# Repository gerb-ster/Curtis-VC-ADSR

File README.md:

# Curtis VC ADSR

A voltage controlled ADSR enveloppe generator based on the CEM 3310

## Status: Finished

- done: first schematic & board design
- done: breadboard and test
- done: design frontpanel
- done: order PCB and build prototype

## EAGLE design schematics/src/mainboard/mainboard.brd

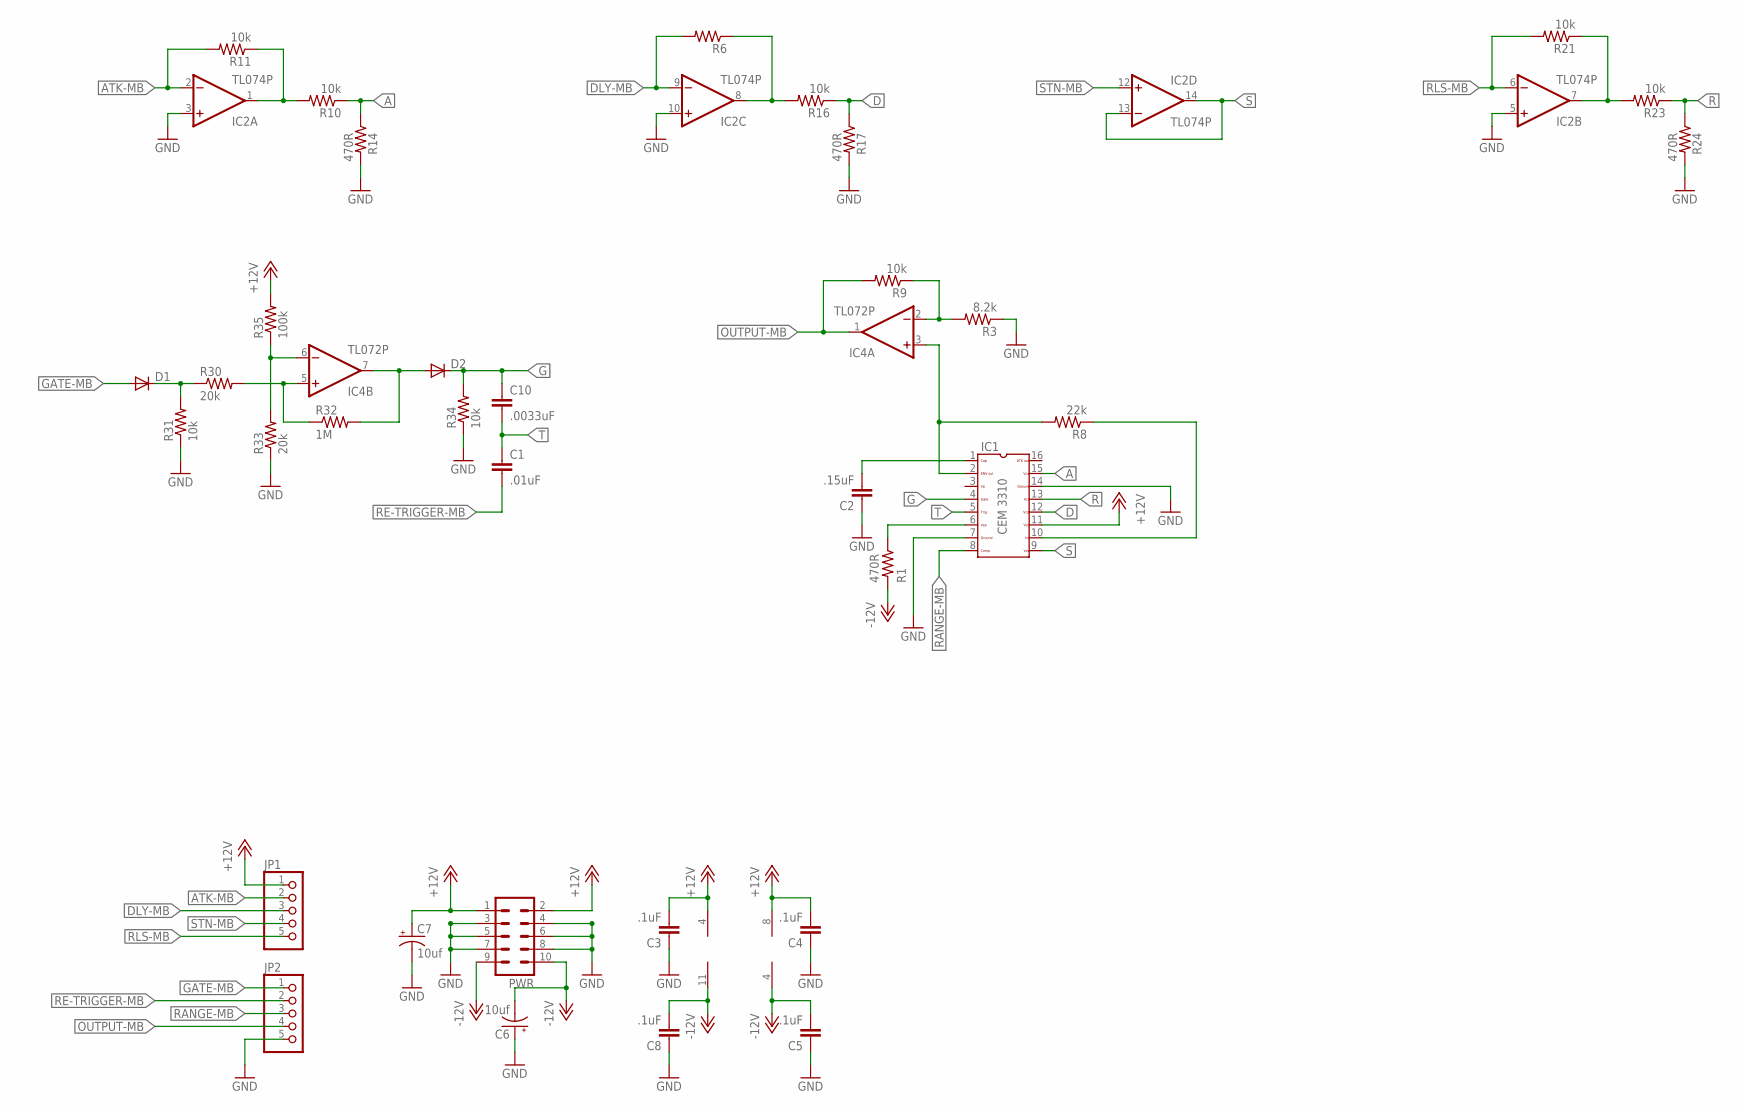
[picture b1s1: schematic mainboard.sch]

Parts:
C1: .01uF; C050-024X044
C2: .15uF; C050-024X044
C3, C4, C5, C8: .1uF; C050-024X044
C6, C7: 10uf; E2,5-5
C10: .0033uF; C050-024X044
D1, D2: 1N4148DO35-7; DO35-7
IC1: CEM3310; DIL16
IC2: TL074P; DIL14
IC4: TL072P; DIL08
JP1, JP2: PINHD-1X5; 1X05
PWR: ML10
R1, R14, R17, R24: 470R; 0207/7
R3: 8.2k; 0207/7
R6, R9, R10, R11, R16, R21, R23, R31, R34: 10k; 0207/7
R8: 22k; 0207/7
R30, R33: 20k; 0207/7
R32: 1M; 0207/7
R35: 100k; 0207/7

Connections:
+12V: C3.2, C4.2, C7.+, IC1.11, IC2.4 (V+), IC4.8 (V+), JP1.1, PWR.1, PWR.2, R35.2
-12V: C5.2, C6.-, C8.2, IC2.11 (V-), IC4.4 (V-), PWR.9, PWR.10, R1.2
A: IC1.15, R10.1, R14.1
ATK-MB: IC2.2 (-IN), JP1.2, R11.2
D: IC1.12, R16.1, R17.1
DLY-MB: IC2.9 (-IN), JP1.3, R6.2
G: C10.1, D2.C, IC1.4, R34.2
GATE-MB: D1.A, JP2.1
GND: C2.1, C3.1, C4.1, C5.1, C6.+, C7.-, C8.1, IC1.7, IC1.14, IC2.3 (+IN), IC2.5 (+IN), IC2.10 (+IN), JP2.5, PWR.3, PWR.4, PWR.5, PWR.6, PWR.7, PWR.8, R3.1, R14.2, R17.2, R24.2, R31.1, R33.1, R34.1
unnamed: IC1.6, R1.1
unnamed: C2.2, IC1.1
unnamed: IC2.1 (OUT), R10.2, R11.1
unnamed: D1.C, R30.1, R31.2
unnamed: IC2.8 (OUT), R6.1, R16.2
unnamed: IC1.2, IC4.3 (+IN), R8.2
unnamed: IC2.7 (OUT), R21.1, R23.2
unnamed: IC4.5 (+IN), R30.2, R32.1
unnamed: IC1.10, R8.1
unnamed: IC4.2 (-IN), R3.2, R9.1
unnamed: D2.A, IC4.7 (OUT), R32.2
unnamed: IC4.6 (-IN), R33.2, R35.1
OUTPUT-MB: IC4.1 (OUT), JP2.4, R9.2
R: IC1.13, R23.1, R24.1
RANGE-MB: IC1.8, JP2.3
RE-TRIGGER-MB: C1.2, JP2.2
RLS-MB: IC2.6 (-IN), JP1.5, R21.2
S: IC1.9, IC2.13 (-IN), IC2.14 (OUT)
STN-MB: IC2.12 (+IN), JP1.4
T: C1.1, C10.2, IC1.5

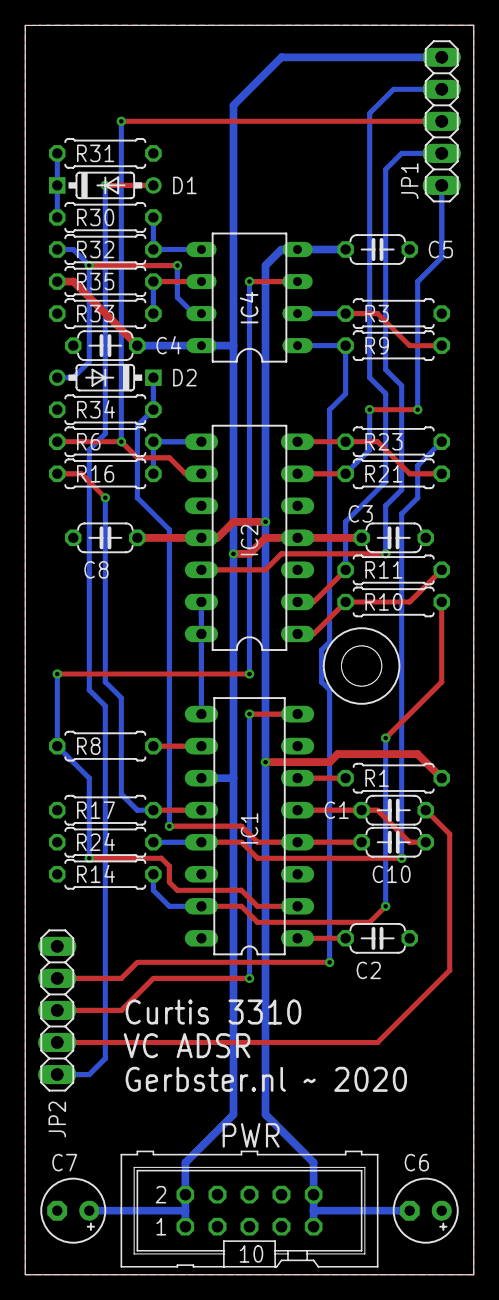
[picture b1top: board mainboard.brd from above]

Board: 2 copper layers, 35.6 x 99.1 mm, 36 parts (0 on the bottom side), 29 nets.

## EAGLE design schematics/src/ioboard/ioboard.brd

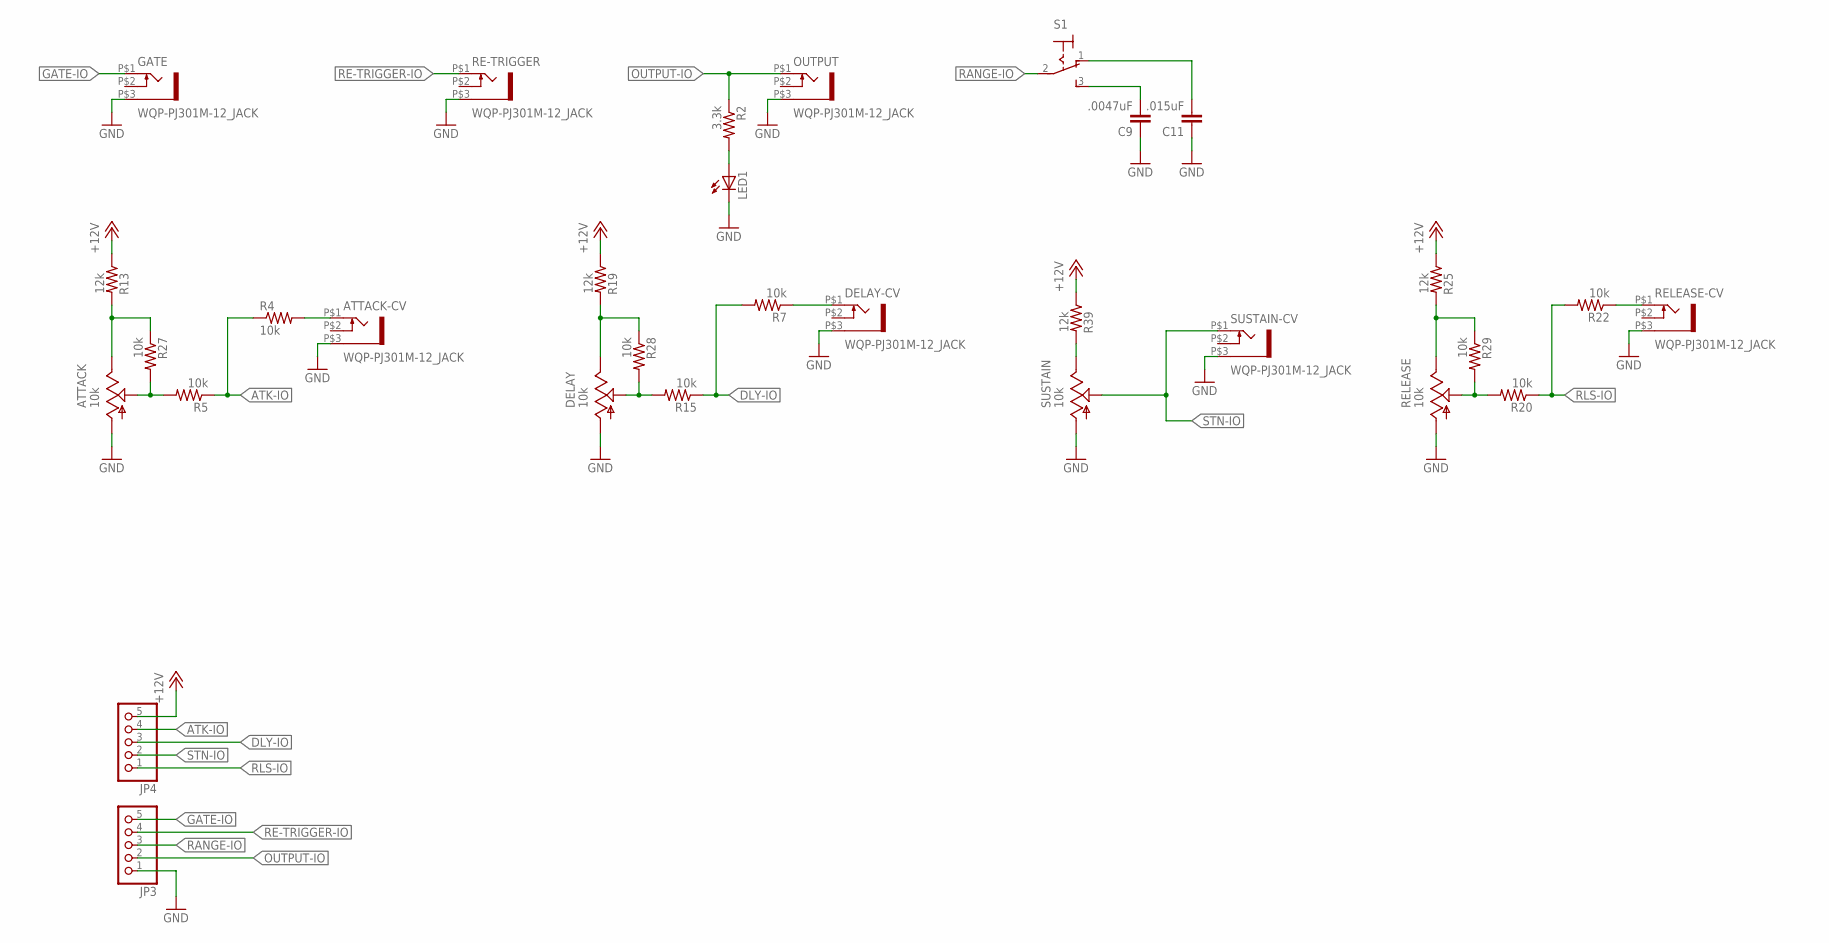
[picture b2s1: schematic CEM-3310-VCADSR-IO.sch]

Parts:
ATTACK: 10k; EVUF
ATTACK-CV: WQP-PJ301M-12_JACK
C9: .0047uF; C050-024X044
C11: .015uF; C050-024X044
DELAY: 10k; EVUF
DELAY-CV: WQP-PJ301M-12_JACK
GATE: WQP-PJ301M-12_JACK
JP3, JP4: PINHD-1X5; 1X05
LED1: LED5MM
OUTPUT: WQP-PJ301M-12_JACK
R2: 3.3k; 0207/7
R4, R5, R7, R15, R20, R22, R27, R28, R29: 10k; 0207/7
R13, R19, R25, R39: 12k; 0207/7
RE-TRIGGER: WQP-PJ301M-12_JACK
RELEASE: 10k; EVUF
RELEASE-CV: WQP-PJ301M-12_JACK
S1: M9040P
SUSTAIN: 10k; EVUF
SUSTAIN-CV: WQP-PJ301M-12_JACK

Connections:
+12V: JP4.5, R13.1, R19.1, R25.1, R39.1
ATK-IO: JP4.4, R4.1, R5.1
ATTACK-CV: ATTACK-CV.P$1 (2), R4.2
DELAY-VC: DELAY-CV.P$1 (2), R7.1
DLY-IO: JP4.3, R7.2, R15.1
GATE-IO: GATE.P$1 (2), JP3.5
GND: ATTACK.1 (A), ATTACK-CV.P$3 (1), C9.1, C11.1, DELAY.1 (A), DELAY-CV.P$3 (1), GATE.P$3 (1), JP3.1, LED1.K (C), OUTPUT.P$3 (1), RE-TRIGGER.P$3 (1), RELEASE.1 (A), RELEASE-CV.P$3 (1), SUSTAIN.1 (A), SUSTAIN-CV.P$3 (1)
unnamed: C9.2, S1.3 (S)
unnamed: C11.2, S1.1 (O)
unnamed: ATTACK.2 (S), R5.2, R27.2
unnamed: ATTACK.3 (E), R13.2, R27.1
unnamed: DELAY.3 (E), R19.2, R28.1
unnamed: DELAY.2 (S), R15.2, R28.2
unnamed: R20.2, R29.2, RELEASE.2 (S)
unnamed: R25.2, R29.1, RELEASE.3 (E)
unnamed: LED1.A, R2.2
unnamed: R39.2, SUSTAIN.3 (E)
OUTPUT-IO: JP3.2, OUTPUT.P$1 (2), R2.1
RANGE-IO: JP3.3, S1.2
RE-TRIGGER-IO: JP3.4, RE-TRIGGER.P$1 (2)
RELEASE-CV: R22.1, RELEASE-CV.P$1 (2)
RLS-IO: JP4.1, R20.1, R22.2
STN-IO: JP4.2, SUSTAIN.2 (S), SUSTAIN-CV.P$1 (2)

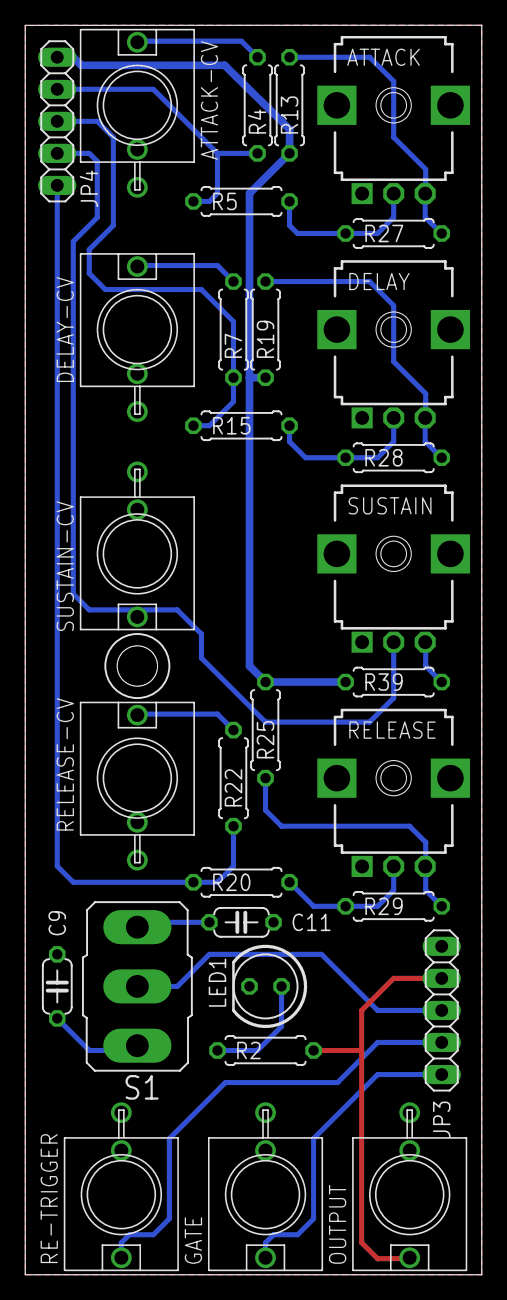
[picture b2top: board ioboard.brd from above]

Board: 2 copper layers, 36.2 x 99.1 mm, 31 parts (0 on the bottom side), 23 nets.

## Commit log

2021-05-01 done
2021-05-07 added files & Structure
2021-05-10 Added Status
2021-05-11 Added Status & Images
2021-08-06 Updated some schematics and docs
2021-08-10 Fixed some bugs and updated documentation
2022-04-20 Some updates & bugfixes
2022-04-22 Fixed schematics & descriptions
2022-05-17 Updated Firmware
2022-05-18 Updated Faceplates
2022-05-18 Fixed issues
2022-05-21 Fixed schematics
2022-05-28 General updates
